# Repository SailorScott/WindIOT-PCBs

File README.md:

# WindIOT-PCBs
 Controller PCB and wind speed and direction PCB

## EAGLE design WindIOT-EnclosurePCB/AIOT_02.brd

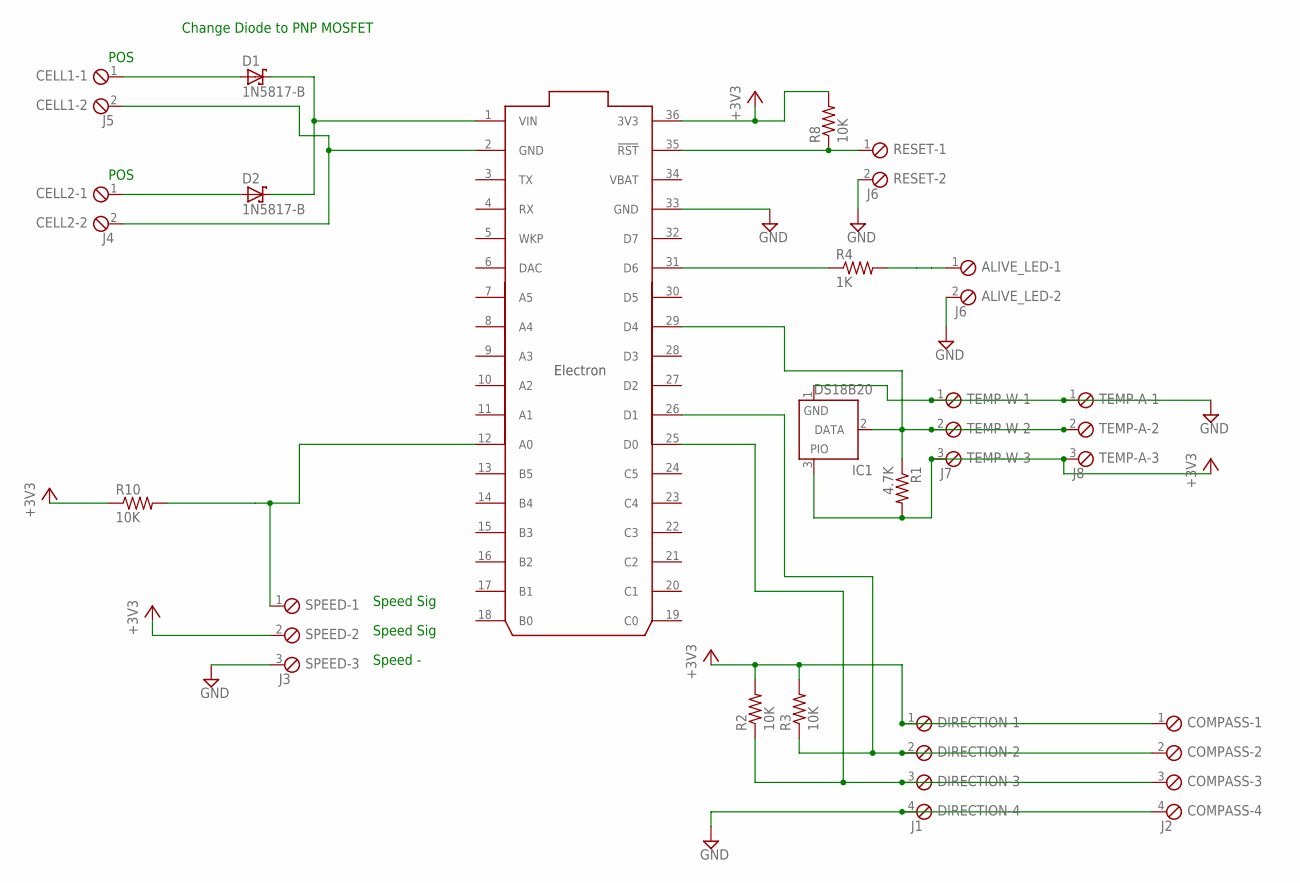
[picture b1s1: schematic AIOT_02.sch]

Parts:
ALIVE_LED: J6; 2POL254
CELL1: J5; 2POL254
CELL2: J4; 2POL254
COMPASS: J2; 4POL254
D1, D2: 1N5817-B; DO41-7.6
DIRECTION: J1; 4POL254
IC1: DS18B20; TO92-
R1: 4.7K; R1210
R2, R3, R8, R10: 10K; R1210
R4: 1K; R1210
RESET: J6; 2POL254
SPEED: J3; 3POL254
TEMP-A: J8; 3POL254
TEMP-W: J7; 3POL254
U$1: ELECTRON_WITH_HEADERS; ELECTRON

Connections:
+3V3: COMPASS.1, DIRECTION.1, IC1.3 (PIO), R1.2, R2.2, R3.2, R8.2, R10.1, SPEED.2, TEMP-A.3, TEMP-W.3, U$1.36 (3V3)
GND: ALIVE_LED.2, CELL1.2, CELL2.2, COMPASS.4, DIRECTION.4, IC1.1 (GND), RESET.2, SPEED.3, TEMP-A.1, TEMP-W.1, U$1.2 (GND), U$1.33 (GND)
unnamed: CELL1.1, D1.A
unnamed: D1.C, D2.C, U$1.1 (VIN)
unnamed: CELL2.1, D2.A
unnamed: R10.2, SPEED.1, U$1.12 (A0)
unnamed: COMPASS.2, DIRECTION.2, R3.1, U$1.26 (D1)
unnamed: ALIVE_LED.1, R4.2
unnamed: COMPASS.3, DIRECTION.3, R2.1, U$1.25 (D0)
unnamed: IC1.2 (DATA), R1.1, TEMP-A.2, TEMP-W.2, U$1.29 (D4)
unnamed: R8.1, RESET.1, U$1.35 (!RST)
unnamed: R4.1, U$1.31 (D6)
VBAT: U$1.34 (VBAT)

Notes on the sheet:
POS
Speed Sig
Speed -
Change Diode to PNP MOSFET

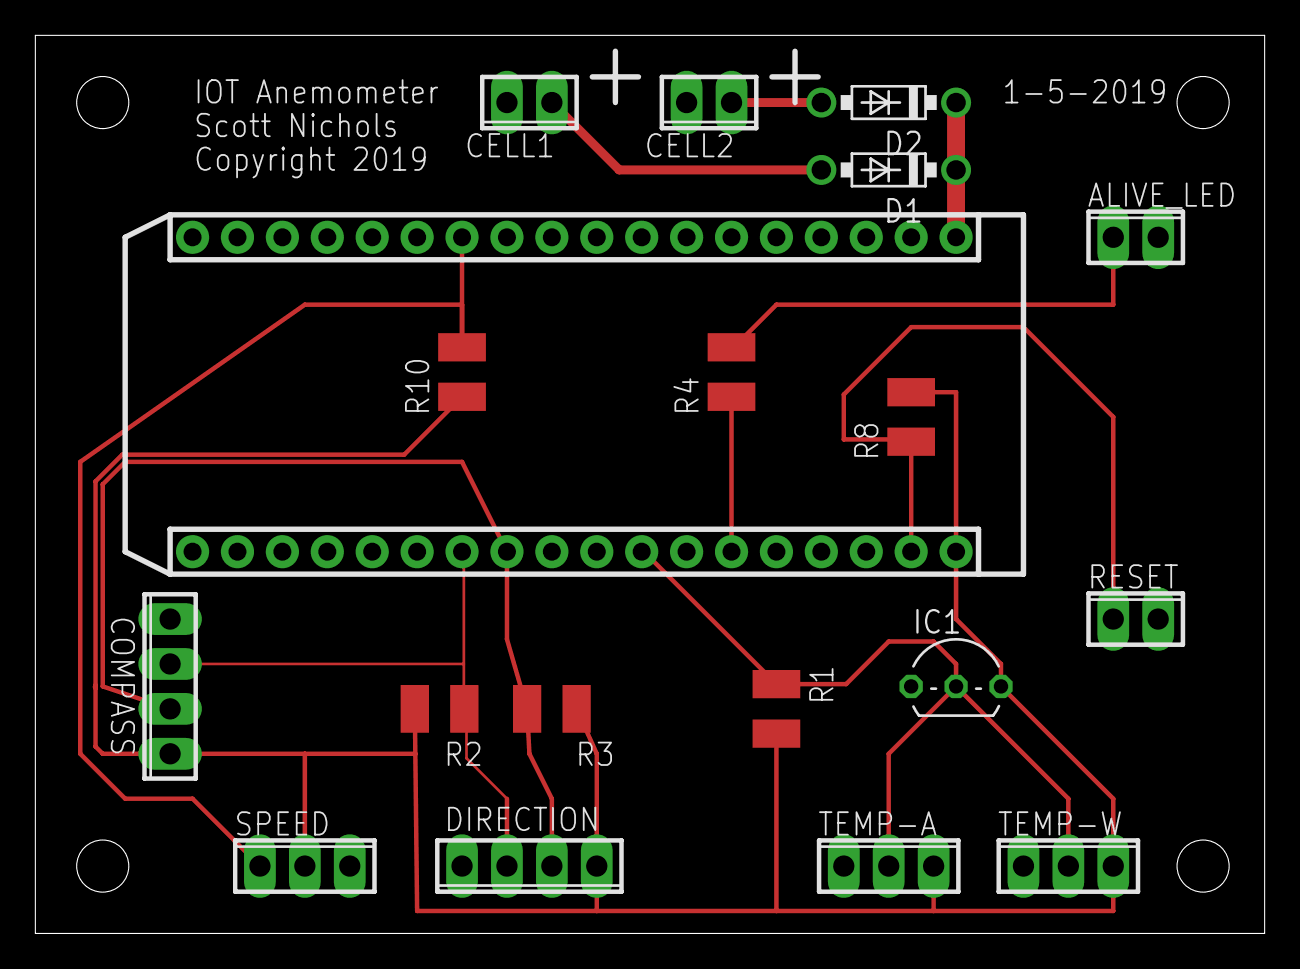
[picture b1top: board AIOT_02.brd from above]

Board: 2 copper layers, 69.5 x 50.8 mm, 19 parts (0 on the bottom side), 12 nets.

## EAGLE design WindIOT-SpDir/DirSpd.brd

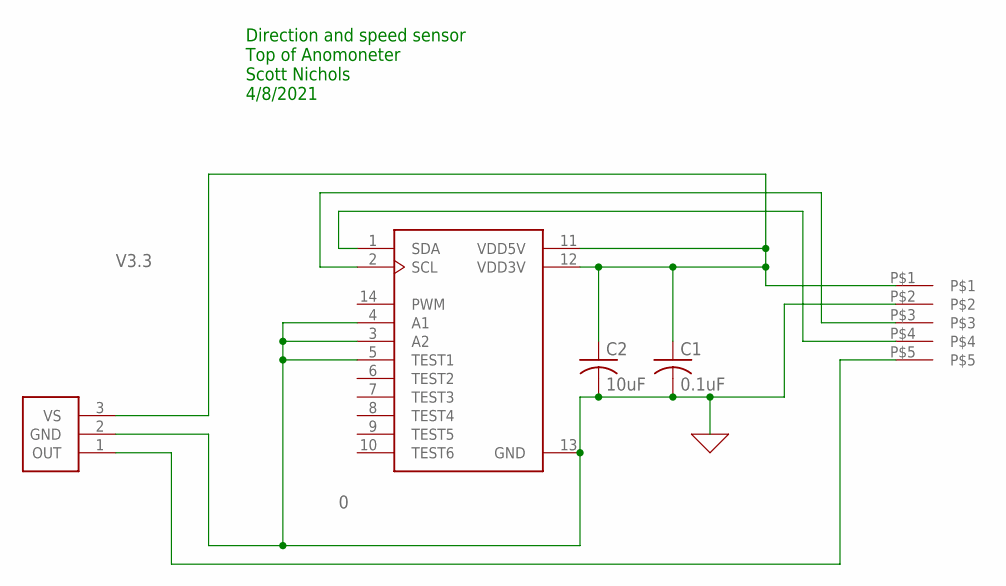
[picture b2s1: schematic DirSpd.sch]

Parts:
C1: 0.1uF; C0805K
C2: 10uF; C0805K
J1: B05B-PASK
U1: AS5048B; TSSOP14
U2: SS451A; TO-92-3

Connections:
0: C1.2, C2.2, J1.P$2, U1.3 (A2), U1.4 (A1), U1.5 (TEST1), U1.13 (GND), U2.2 (GND)
unnamed: J1.P$5, U2.1 (OUT)
unnamed: J1.P$3, U1.2 (SCL)
unnamed: J1.P$4, U1.1 (SDA)
V3.3: C1.1, C2.1, J1.P$1, U1.11 (VDD5V), U1.12 (VDD3V), U2.3 (VS)

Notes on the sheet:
Direction and speed sensor Top of Anomoneter Scott Nichols 4/8/2021

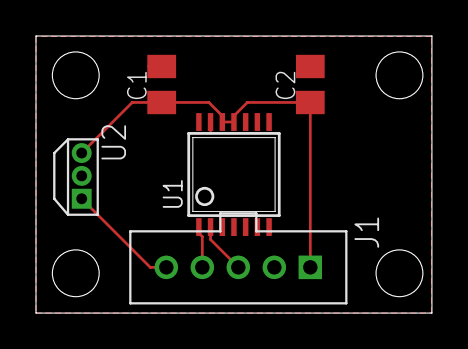
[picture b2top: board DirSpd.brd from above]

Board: 2 copper layers, 22.0 x 15.4 mm, 5 parts (0 on the bottom side), 5 nets.

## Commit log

2021-10-26 First push to Github

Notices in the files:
WindIOT-EnclosurePCB/AIOT_02.brd:
Copyright 2019
parts and their libraries:
Particle-Devices: Licensing: Designed by Particle.
